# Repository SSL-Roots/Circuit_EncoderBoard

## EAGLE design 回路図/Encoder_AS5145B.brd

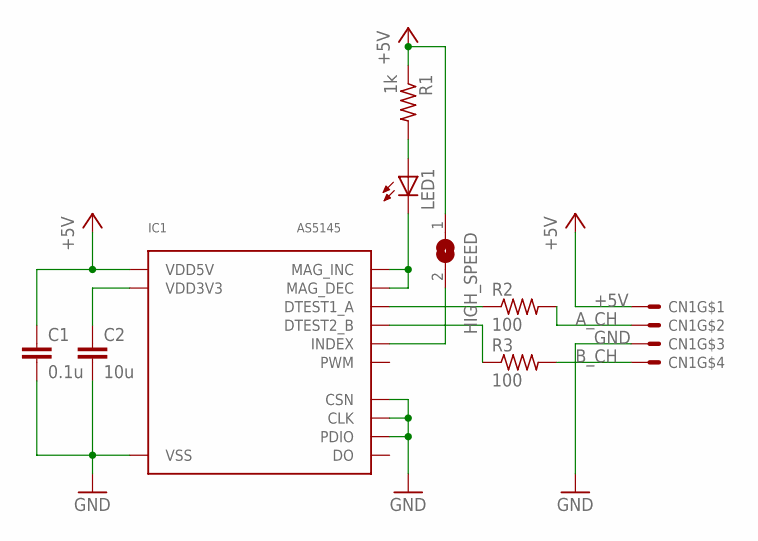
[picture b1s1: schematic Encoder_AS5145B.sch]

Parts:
C1: 0.1u; C0603
C2: 10u; C2012
CN1: 4B-XH-AS4B; S4B-XH-A
HIGH_SPEED: SJ
IC1: AS5145; SSOP16-WIDE
LED1: LEDCHIPLED_0805; CHIPLED_0805
R1: 1k; R1608
R2, R3: 100; R1608

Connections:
+5V: C1.1, CN1.1, HIGH_SPEED.1, IC1.16 (VDD5V), R1.1
A_CH: CN1.2, R2.2
B_CH: CN1.4, R3.2
GND: C1.2, C2.2, CN1.3, IC1.7 (VSS), IC1.8 (PDIO), IC1.10 (CLK), IC1.11 (CSN)
unnamed: LED1.A, R1.2
unnamed: IC1.4 (DTEST2_B), R3.1
unnamed: IC1.3 (DTEST1_A), R2.1
unnamed: HIGH_SPEED.2, IC1.6 (INDEX)
unnamed: C2.1, IC1.15 (VDD3V3)
unnamed: IC1.1 (MAG_INC), IC1.2 (MAG_DEC), LED1.C

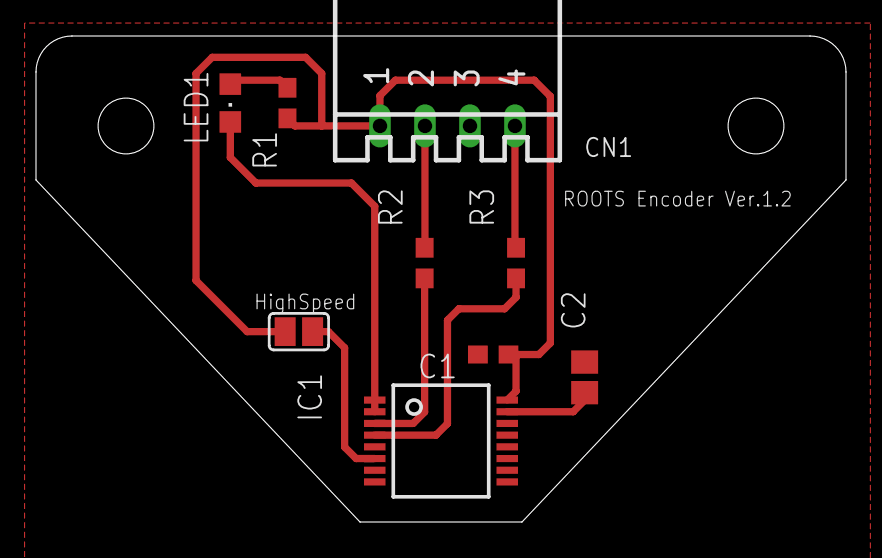
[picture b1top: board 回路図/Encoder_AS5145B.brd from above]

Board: 2 copper layers, 45.0 x 27.0 mm, 9 parts (0 on the bottom side), 10 nets.

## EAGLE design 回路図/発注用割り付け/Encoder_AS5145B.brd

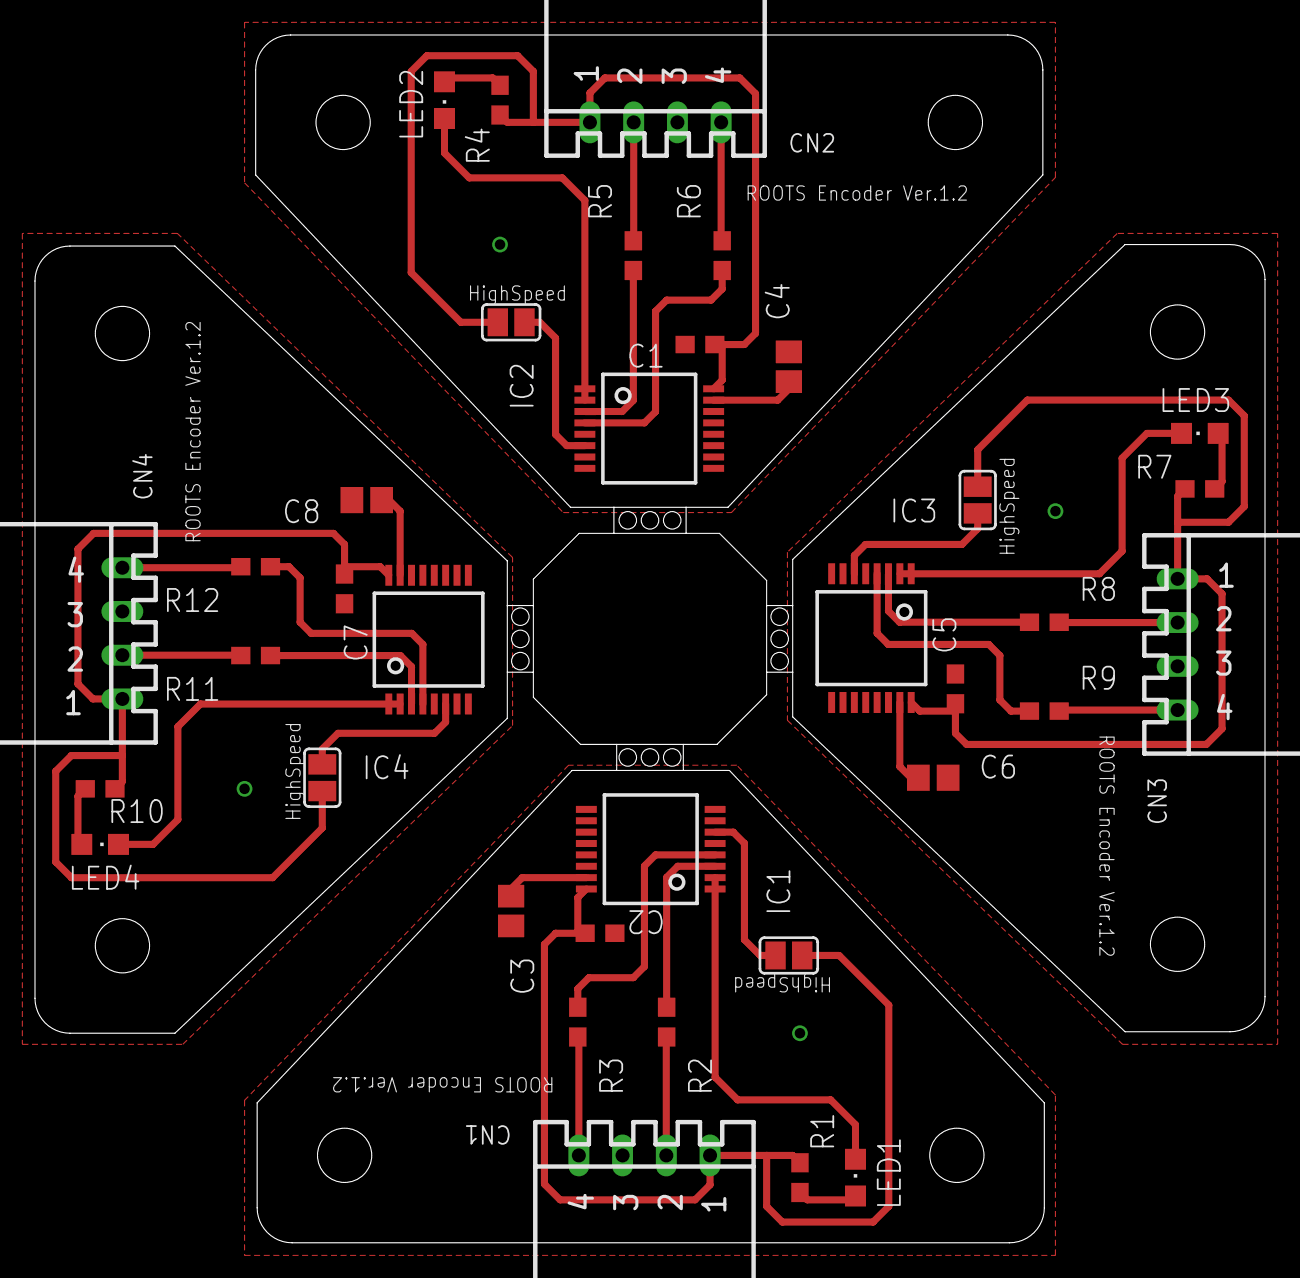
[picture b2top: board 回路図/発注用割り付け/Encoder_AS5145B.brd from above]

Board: 2 copper layers, 70.3 x 69.0 mm, 36 parts (0 on the bottom side), 40 nets.

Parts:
C1, C2, C5, C7: 0.1u; C0603
C3, C4, C6, C8: 10u; C2012
CN1, CN2, CN3, CN4: 4B-XH-AS4B; S4B-XH-A
HIGH_SPEED, HIGH_SPEED1, HIGH_SPEED2, HIGH_SPEED3: SJ
IC1, IC2, IC3, IC4: AS5145; SSOP16-WIDE
LED1, LED2, LED3, LED4: CHIPLED_0805
R1, R4, R7, R10: 1k; R1608
R2, R3, R5, R6, R8, R9, R11, R12: 100; R1608

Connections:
+5V: C2.1, CN1.1, HIGH_SPEED.1, IC1.16, R1.1
+5V1: C1.1, CN2.1, HIGH_SPEED1.1, IC2.16, R4.1
+5V2: C5.1, CN3.1, HIGH_SPEED2.1, IC3.16, R7.1
+5V3: C7.1, CN4.1, HIGH_SPEED3.1, IC4.16, R10.1
GND: C2.2, C3.2, CN1.3, IC1.7, IC1.8, IC1.10, IC1.11
GND1: C1.2, C4.2, CN2.3, IC2.7, IC2.8, IC2.10, IC2.11
GND2: C5.2, C6.2, CN3.3, IC3.7, IC3.8, IC3.10, IC3.11
GND3: C7.2, C8.2, CN4.3, IC4.7, IC4.8, IC4.10, IC4.11
unnamed: LED1.A, R1.2
unnamed: IC1.4, R3.1
unnamed: IC1.3, R2.1
unnamed: CN1.2, R2.2
unnamed: CN1.4, R3.2
unnamed: HIGH_SPEED.2, IC1.6
unnamed: C3.1, IC1.15
unnamed: IC2.1, IC2.2, LED2.C
unnamed: IC1.1, IC1.2, LED1.C
unnamed: LED2.A, R4.2
unnamed: IC2.3, R5.1
unnamed: CN2.2, R5.2
unnamed: CN2.4, R6.2
unnamed: IC2.4, R6.1
unnamed: C4.1, IC2.15
unnamed: HIGH_SPEED1.2, IC2.6
unnamed: IC3.1, IC3.2, LED3.C
unnamed: LED3.A, R7.2
unnamed: IC3.3, R8.1
unnamed: CN3.2, R8.2
unnamed: CN3.4, R9.2
unnamed: IC3.4, R9.1
unnamed: C6.1, IC3.15
unnamed: HIGH_SPEED2.2, IC3.6
unnamed: IC4.1, IC4.2, LED4.C
unnamed: LED4.A, R10.2
unnamed: IC4.3, R11.1
unnamed: CN4.2, R11.2
unnamed: CN4.4, R12.2
unnamed: IC4.4, R12.1
unnamed: C8.1, IC4.15
unnamed: HIGH_SPEED3.2, IC4.6

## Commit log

2018-05-24 Add files via upload
    部品表を修正
2018-05-24 Delete BallSensor - シート1.pdf
    ボールセンサーの部品表だったので削除
2020-04-20 Create LICENSE
